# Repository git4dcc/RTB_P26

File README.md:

# RTB_P26

This is a **motor DCC decoder development board** you can plug right into a breadboard. It has all the necessary hardware for a DCC decoder, except for the microcontroller.

<details>
<summary>See also</summary>

- [RTB_D16](/../../../../git4dcc/RTB_D16) (DCC Decoder)

</details>

<details>
<summary>User Guides</summary>

- User Guide - DE (to be done)
- User Guide - EN (to be done)

</details>

# Hardware
My PCB layout uses SMD footprints with mainly 0603 parts. With some experience handsoldering is good to use.

## PCB
- 2-layer PCB, FR4, 1.6mm
- Dimensions: 42mm x 22mm
- VDD voltage: 3.3V, 50mA (optional 5V using a different LDO)
- 18V max DCC voltage
- Railcom transmitter
- Inrush limiter: TPS22810
- H-Bridge: DRV8231

## Kicad
[Schematic](doc/P26_schematic.pdf) | [Layout](doc/P26_layout.pdf) | [Gerber](gerber/P26_0.zip)

<details>
<summary>Dependency</summary>
<br>

:yellow_circle: Requires my Kicad project library [RTB_SamacSys](/../../../../git4dcc/RTB_SamacSys) in the same directory tree.

</details>

# Images

This project is intended for hobby use only and is distributed in accordance with the Apache License 2.0 agreement.

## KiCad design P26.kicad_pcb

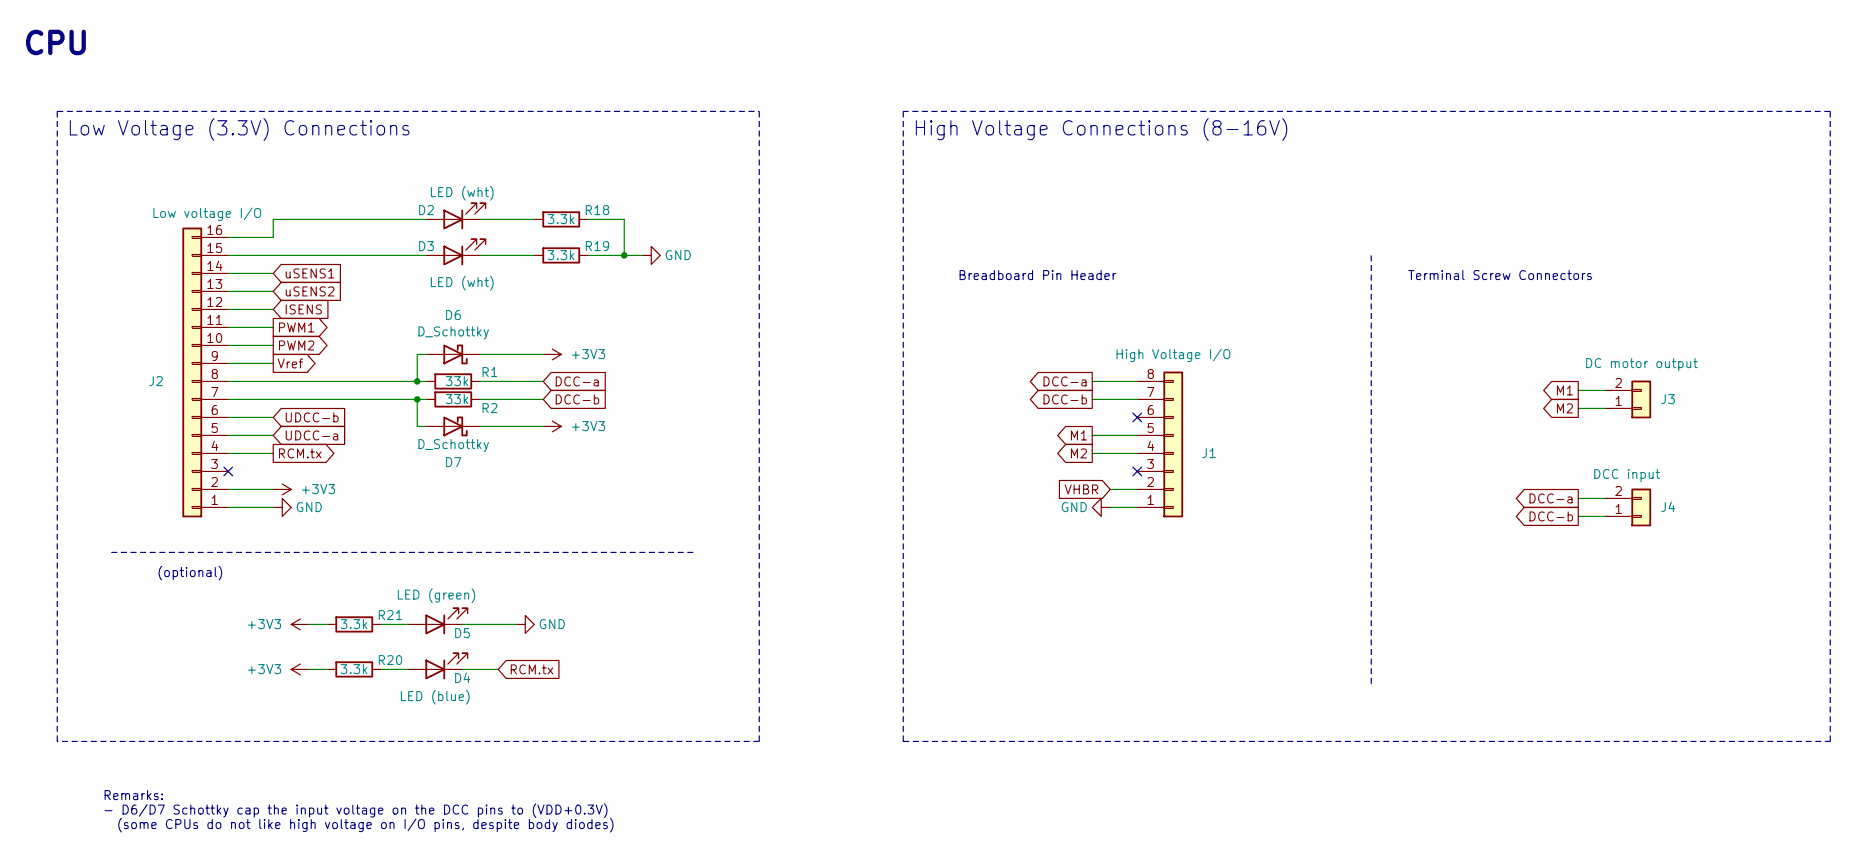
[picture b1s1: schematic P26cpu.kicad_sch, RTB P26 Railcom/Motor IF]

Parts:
D2, D3: LED (wht); LED_0603_1608Metric; JLCPCB C2290
D4: LED (blue); LED_0603_1608Metric; JLCPCB C965807
D5: LED (green); LED_0603_1608Metric; JLCPCB C84264
D6, D7: D_Schottky; SM5819L2TP; JLCPCB C3012686
J1: High Voltage I/O; PinHeader_1x08_P2.54mm_Vertical
J2: Low voltage I/O; PinHeader_1x16_P2.54mm_Vertical
J3: DC motor output; 1725656
J4: DCC input; 1725656
R1, R2: 33k; R_0603_1608Metric; JLCPCB C4216
R18, R19, R20, R21: 3.3k; R_0603_1608Metric; JLCPCB C22978

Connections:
+3V3: D6.1 (K), D7.1 (K), J2.2, R20.2, R21.2; also elsewhere on the board
DCC-a: J1.8, J4.2, R1.1; also elsewhere on the board
DCC-b: J1.7, J4.1, R2.1; also elsewhere on the board
GND: D5.1 (K), J1.1, J2.1, R18.1, R19.1; also elsewhere on the board
ISENS: J2.12; also elsewhere on the board
M1: J1.5, J3.2; also elsewhere on the board
M2: J1.4, J3.1; also elsewhere on the board
unnamed: D2.2 (A), J2.16
unnamed: D2.1 (K), R18.2
unnamed: D3.2 (A), J2.15
unnamed: D3.1 (K), R19.2
unnamed: D4.2 (A), R20.1
unnamed: D5.2 (A), R21.1
unnamed: D6.2 (A), J2.8, R1.2
unnamed: D7.2 (A), J2.7, R2.2
PWM1: J2.11; also elsewhere on the board
PWM2: J2.10; also elsewhere on the board
RCM.tx: D4.1 (K), J2.4; also elsewhere on the board
UDCC-a: J2.5; also elsewhere on the board
UDCC-b: J2.6; also elsewhere on the board
VHBR: J1.2; also elsewhere on the board
Vref: J2.9; also elsewhere on the board
uSENS1: J2.14; also elsewhere on the board
uSENS2: J2.13; also elsewhere on the board

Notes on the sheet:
CPU
High Voltage Connections (8-16V)
Terminal Screw Connectors
(optional)
Breadboard Pin Header
Low Voltage (3.3V) Connections
Remarks: - D6/D7 Schottky cap the input voltage on the DCC pins to (VDD+0.3V) (some CPUs do not like high voltage on I/O pins, despite body diodes)

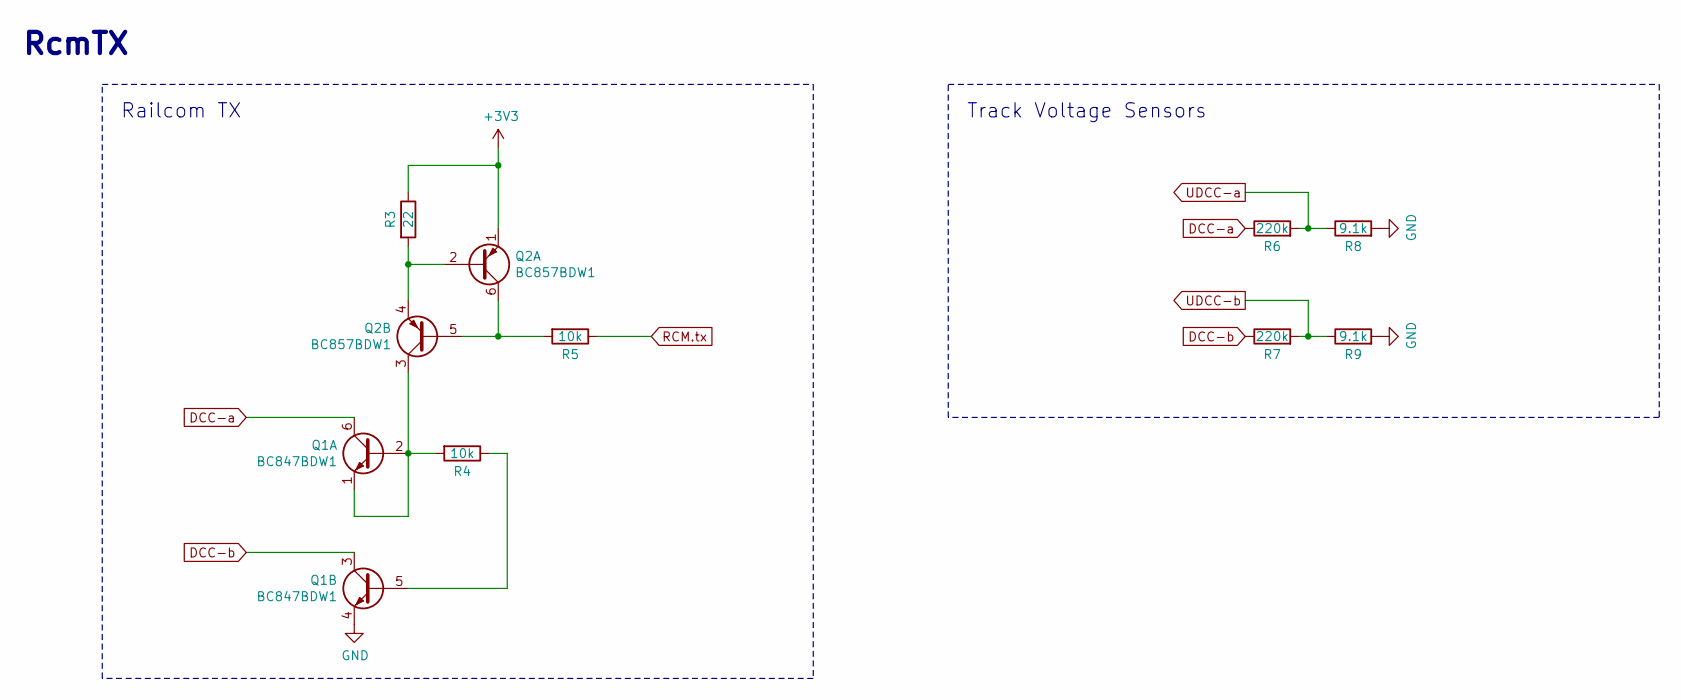
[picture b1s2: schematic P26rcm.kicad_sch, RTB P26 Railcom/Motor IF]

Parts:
Q1: BC847BDW1; SOT-363_SC-70-6; JLCPCB C164103
Q2: BC857BDW1; SOT-363_SC-70-6; JLCPCB C383198
R3: 22; R_0603_1608Metric; JLCPCB C23345
R4, R5: 10k; R_0603_1608Metric; JLCPCB C25804
R6, R7: 220k; R_0603_1608Metric; JLCPCB C22961
R8, R9: 9.1k; R_0603_1608Metric; JLCPCB C23260

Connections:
+3V3: Q2.1 (E1), R3.1; also elsewhere on the board
DCC-a: Q1.6 (C1), R6.1; also elsewhere on the board
DCC-b: Q1.3 (C2), R7.1; also elsewhere on the board
GND: Q1.4 (E2), R8.2, R9.2; also elsewhere on the board
unnamed: Q1.1 (E1), Q1.2 (B1), Q2.3 (C2), R4.2
unnamed: Q1.5 (B2), R4.1
unnamed: Q2.2 (B1), Q2.4 (E2), R3.2
unnamed: Q2.5 (B2), Q2.6 (C1), R5.2
RCM.tx: R5.1; also elsewhere on the board
UDCC-a: R6.2, R8.1; also elsewhere on the board
UDCC-b: R7.2, R9.1; also elsewhere on the board

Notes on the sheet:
RcmTX
Railcom TX
Track Voltage Sensors

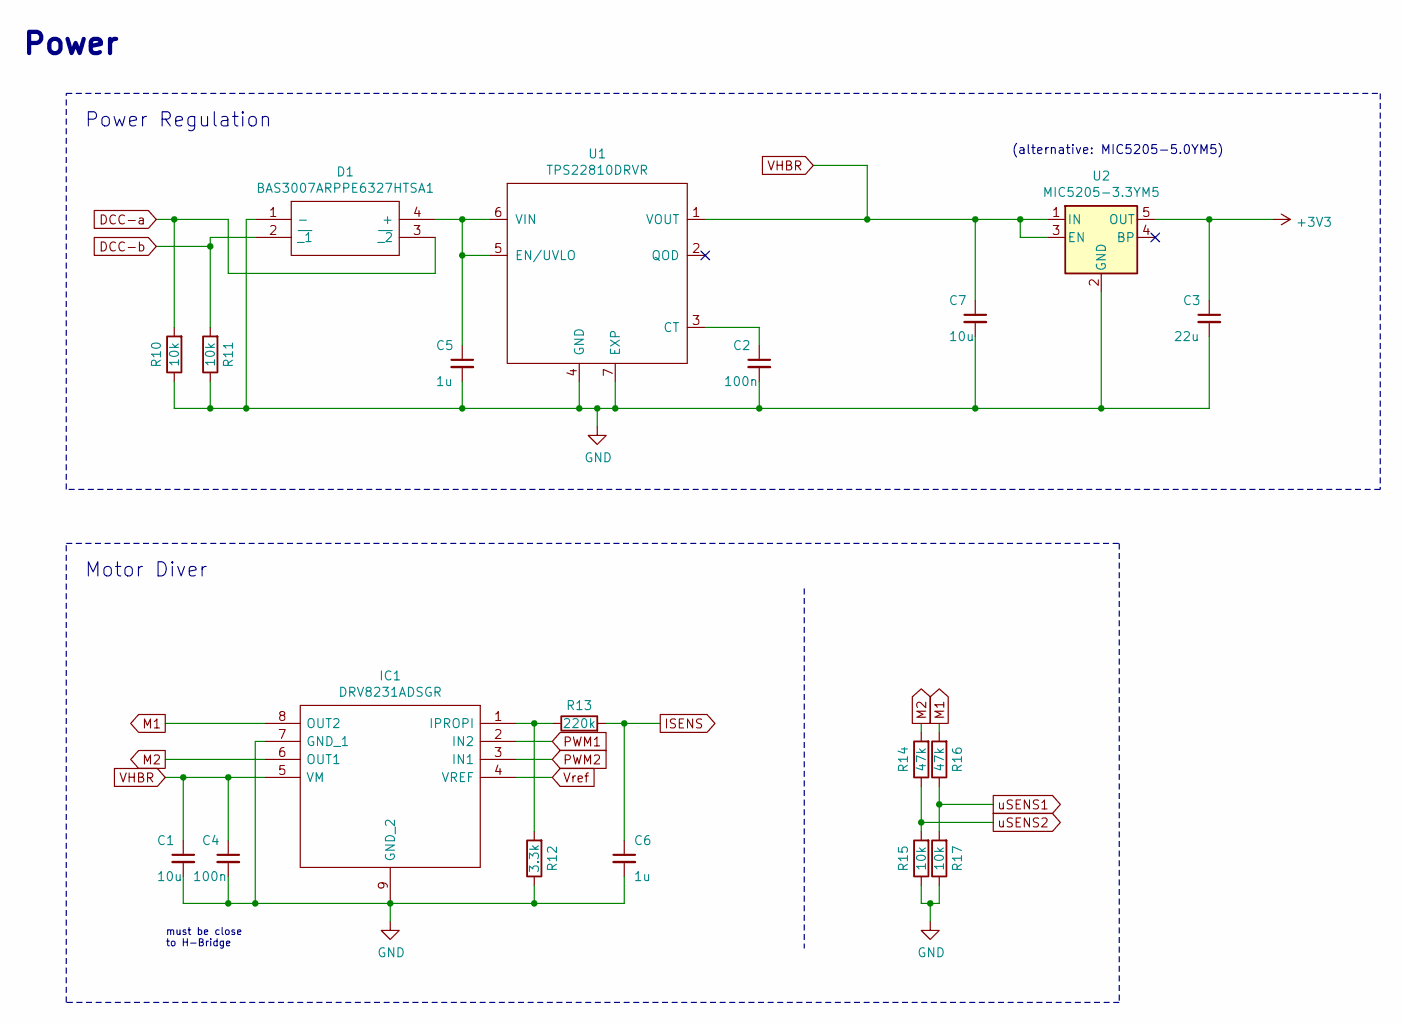
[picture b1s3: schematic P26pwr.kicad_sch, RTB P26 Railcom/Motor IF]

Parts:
C1, C7: 10u; C_0603_1608Metric; JLCPCB C96446
C2, C4: 100n; C_0603_1608Metric; JLCPCB C14663
C3: 22u; C_0603_1608Metric; JLCPCB C59461
C5, C6: 1u; C_0603_1608Metric; JLCPCB C15849
D1: BAS3007ARPPE6327HTSA1; BF998215; JLCPCB C6430958
IC1: DRV8231ADSGR; SON50P200X200X80-9N; JLCPCB C5139865
R10, R11, R15, R17: 10k; R_0603_1608Metric; JLCPCB C25804
R12: 3.3k; R_0603_1608Metric; JLCPCB C22978
R13: 220k; R_0603_1608Metric; JLCPCB C22961
R14, R16: 47k; R_0603_1608Metric; JLCPCB C25819
U1: TPS22810DRVR; DFN-6-1EP_2x2mm_P0.65mm_EP1x1.6mm; JLCPCB C527679
U2: MIC5205-3.3YM5; SOT-23-5; JLCPCB C37970

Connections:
+3V3: C3.1, U2.5 (OUT); also elsewhere on the board
DCC-a: D1.3 (~_2), R10.2; also elsewhere on the board
DCC-b: D1.2 (~_1), R11.2; also elsewhere on the board
GND: C1.2, C2.2, C3.2, C4.2, C5.2, C6.2, C7.2, D1.1 (-), IC1.7 (GND_1), IC1.9 (GND_2), R10.1, R11.1, R12.1, R15.1, R17.1, U1.4 (GND), U1.7 (EXP), U2.2 (GND); also elsewhere on the board
ISENS: C6.1, R13.2; also elsewhere on the board
M1: IC1.8 (OUT2), R16.2; also elsewhere on the board
M2: IC1.6 (OUT1), R14.2; also elsewhere on the board
unnamed: C5.1, D1.4 (+), U1.5 (EN/UVLO), U1.6 (VIN)
unnamed: IC1.1 (IPROPI), R12.2, R13.1
unnamed: C2.1, U1.3 (CT)
PWM1: IC1.2 (IN2); also elsewhere on the board
PWM2: IC1.3 (IN1); also elsewhere on the board
VHBR: C1.1, C4.1, C7.1, IC1.5 (VM), U1.1 (VOUT), U2.1 (IN), U2.3 (EN); also elsewhere on the board
Vref: IC1.4 (VREF); also elsewhere on the board
uSENS1: R16.1, R17.2; also elsewhere on the board
uSENS2: R14.1, R15.2; also elsewhere on the board

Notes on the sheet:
must be close to H-Bridge
Motor Diver
Power Regulation
Power
(alternative: MIC5205-5.0YM5)

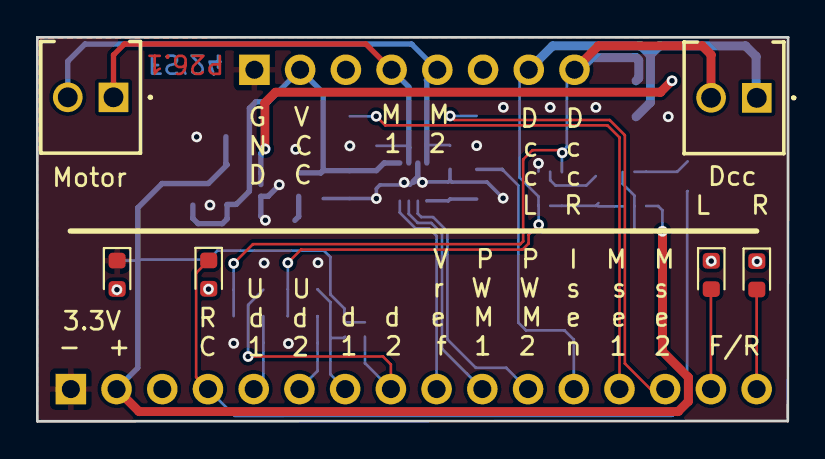
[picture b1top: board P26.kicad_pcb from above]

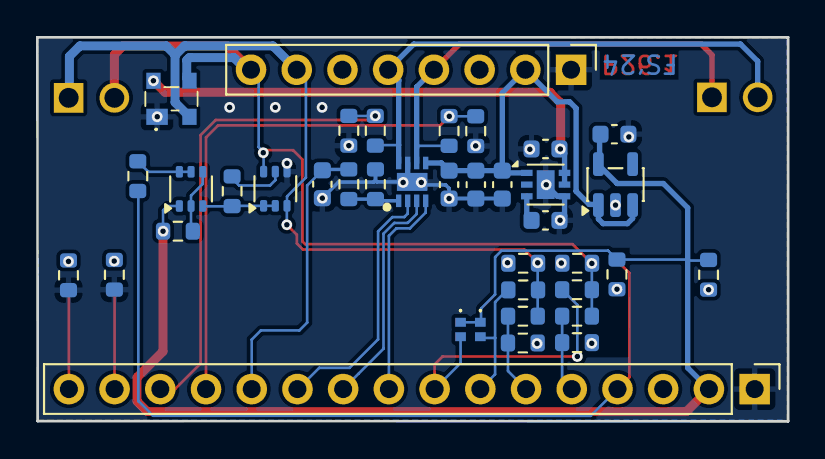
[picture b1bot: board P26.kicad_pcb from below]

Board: 2 copper layers, 41.7 x 21.3 mm, 44 parts (38 on the bottom side), 31 nets.

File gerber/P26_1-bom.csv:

Value,Designator,Footprint,JLCPCB Part#,Description
100n,"C2,C4",Capacitor_SMD:C_0603_1608Metric,C14663,100nF 50V X7R ñ10% 0603 Multilayer Ceramic Capacitors MLCC - SMD/SMT ROHS
22u,C3,Capacitor_SMD:C_0603_1608Metric,C59461,22uF 6.3V X5R ñ20% 0603 Multilayer Ceramic Capacitors MLCC - SMD/SMT ROHS
1u,"C5,C6",Capacitor_SMD:C_0603_1608Metric,C15849,1uF 50V X5R ñ10% 0603 Multilayer Ceramic Capacitors MLCC - SMD/SMT ROHS
10u,"C1,C7",Capacitor_SMD:C_0603_1608Metric,C96446,10uF 25V X5R ñ20% 0603 Multilayer Ceramic Capacitors MLCC - SMD/SMT ROHS
BAS3007ARPPE6327HTSA1,D1,BF998215,C6430958,30V 350uA@30V 5A 600mV@700mA 900mA SOT-143 Schottky Diodes ROHS
LED (wht),"D2,D3",LED_SMD:LED_0603_1608Metric,C2290,100mW 120ø 2.6V~3.1V 360mcd 5mA White 0603 LED Indication - Discrete ROHS
LED (blue),D4,LED_SMD:LED_0603_1608Metric,C965807,120ø 20mA 3.3V 300mcd 455nm~475nm 470nm 70mW Blue Water Clear op View Mount 0603 LED Indication - Discrete ROHS
LED (green),D5,LED_SMD:LED_0603_1608Metric,C84264,-30?~+85? 1.6V~2.6V 13mcd 140ø 25mA 565nm~578nm 576nm 65mW Yellow Green 0603 LED Indication - Discrete ROHS
D_Schottky,"D6,D7",RTB:SM5819L2TP,C3012686,-40?~+125? 200mA 30uA@30V 3A 40V 480mV@200mA SOD-923F Schottky Diodes ROHS
DRV8231ADSGR,IC1,SON50P200X200X80-9N,C5139865,"DRV8231: 4.5-V to 33-V, 600-m, shunt"
BC847BDW1,Q1,Package_TO_SOT_SMD:SOT-363_SC-70-6,C164103,"-55?~+150? 1 NPN + 1 PNP 100MHz 100mA 15nA 200@2.0mA,5.0V 380mW 45V 600mV@10mA,0.5mA 6V NPN+PNP SOT-363(SC-88) Bipolar (BJT) ROHS"
BC857BDW1,Q2,Package_TO_SOT_SMD:SOT-363_SC-70-6,C383198,"-55?~+150? 100MHz 100mA 150@2.0mA,5.0V 15nA 250mW 45V 5V 650mV PNP SOT-363(SC-88) Bipolar (BJT) ROHS"
33k,"R1,R2",Resistor_SMD:R_0603_1608Metric,C4216,-55?~+155? 100mW 33kê 75V Thick Film Resistor ñ1% ñ100ppm/? 0603 Chip Resistor - Surface Mount ROHS
47k,"R14,R16",Resistor_SMD:R_0603_1608Metric,C25819,-55?~+155? 100mW 47kê 75V Thick Film Resistor ñ1% ñ100ppm/? 0603 Chip Resistor - Surface Mount ROHS
3.3k,"R12,R18,R19,R20,R21",Resistor_SMD:R_0603_1608Metric,C22978,-55?~+155? 100mW 3.3kê 75V Thick Film Resistor ñ1% ñ100ppm/? 0603 Chip Resistor - Surface Mount ROHS
22,R3,Resistor_SMD:R_0603_1608Metric,C23345,-55?~+155? 100mW 22ê 75V Thick Film Resistor ñ1% ñ100ppm/? 0603 Chip Resistor - Surface Mount ROHS
10k,"R4,R5,R10,R11,R15,R17",Resistor_SMD:R_0603_1608Metric,C25804,-55?~+155? 100mW 10kê 75V Thick Film Resistor ñ1% ñ100ppm/? 0603 Chip Resistor - Surface Mount ROHS
220k,"R6,R7,R13",Resistor_SMD:R_0603_1608Metric,C22961,-55?~+155? 100mW 220kê 75V Thick Film Resistor ñ1% ñ100ppm/? 0603 Chip Resistor - Surface Mount ROHS
9.1k,"R8,R9",Resistor_SMD:R_0603_1608Metric,C23260,-55?~+155? 100mW 75V 9.1kê Thick Film Resistor ñ1% ñ100ppm/? 0603 Chip Resistor - Surface Mount ROHS
TPS22810DRVR,U1,Package_DFN_QFN:DFN-6-1EP_2x2mm_P0.65mm_EP1x1.6mm,C527679,-40?~+105? 1 2.7V~18V 3A 79mê Active High Load Switch Undervoltage Protection(UVP) WSON-6-EP(2x2) Power Distribution Switches ROHS
MIC5205-3.3YM5,U2,Package_TO_SOT_SMD:SOT-23-5,C37970,"-40?~+125?@(Tj) 1 150mA 16V 3.3V 350mV@(150mA) 600uA 75dB@(100Hz) Fixed Over Current Protection Positive SOT-23-5 Voltage Regulators - Linear, Low Drop Out (LDO) Regulators ROHS"

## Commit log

2024-11-02 initial
2025-09-07 mod: optimized for PCB assembly
2025-10-21 mod: conversion to KiCad 9
2026-02-20 Update links in README.md to relative paths
2026-02-20 git mirror test
